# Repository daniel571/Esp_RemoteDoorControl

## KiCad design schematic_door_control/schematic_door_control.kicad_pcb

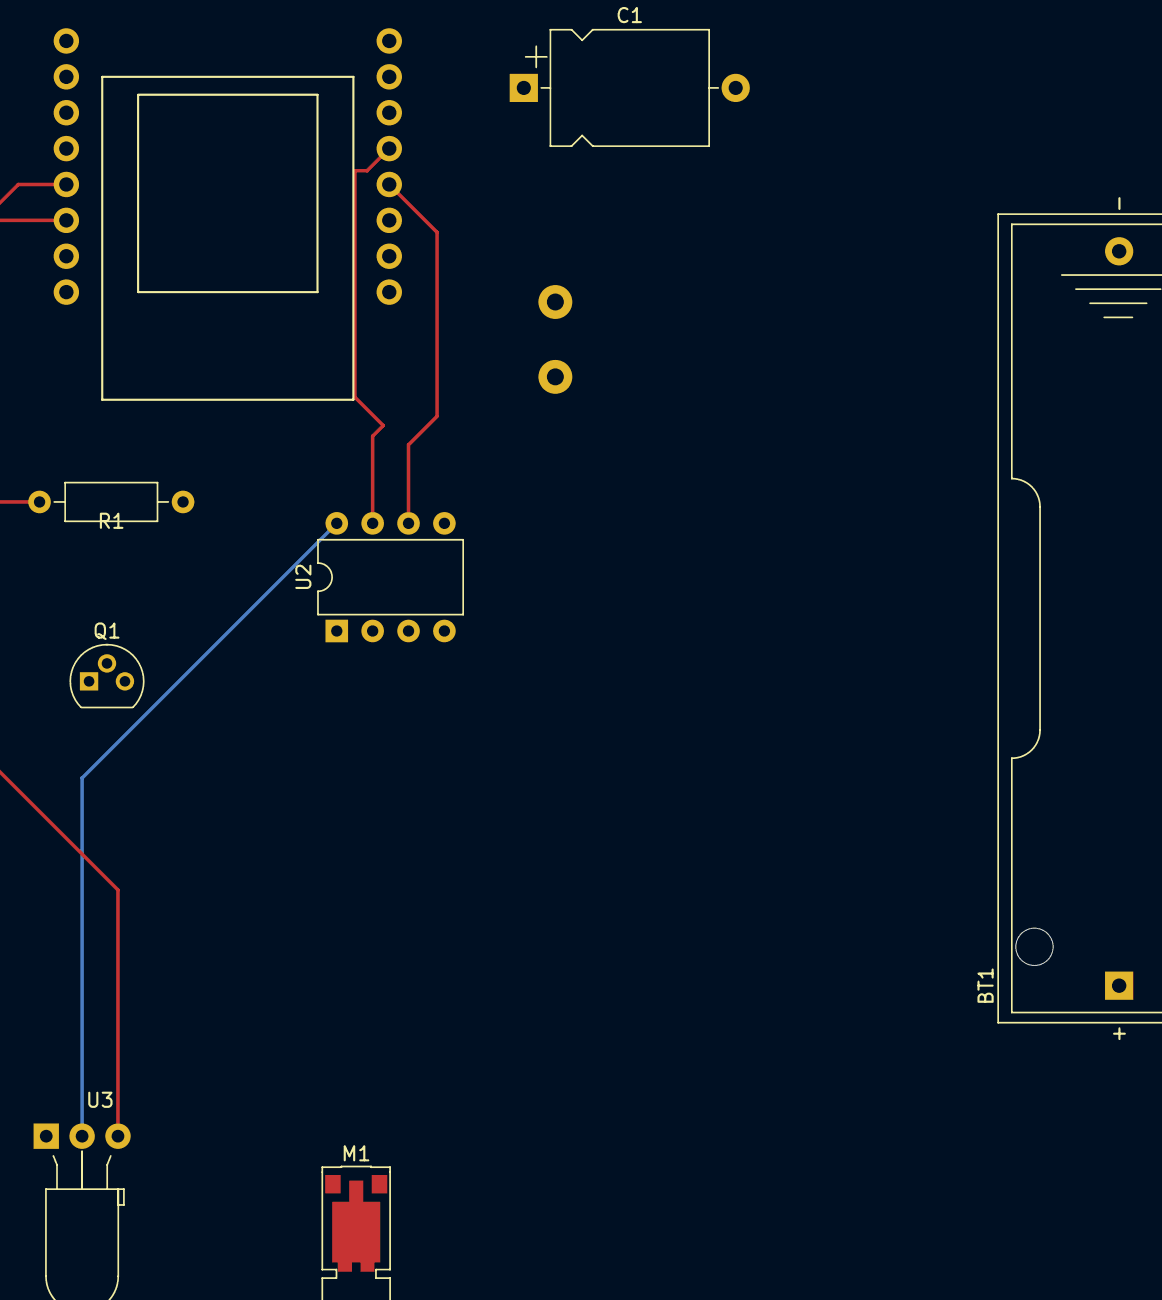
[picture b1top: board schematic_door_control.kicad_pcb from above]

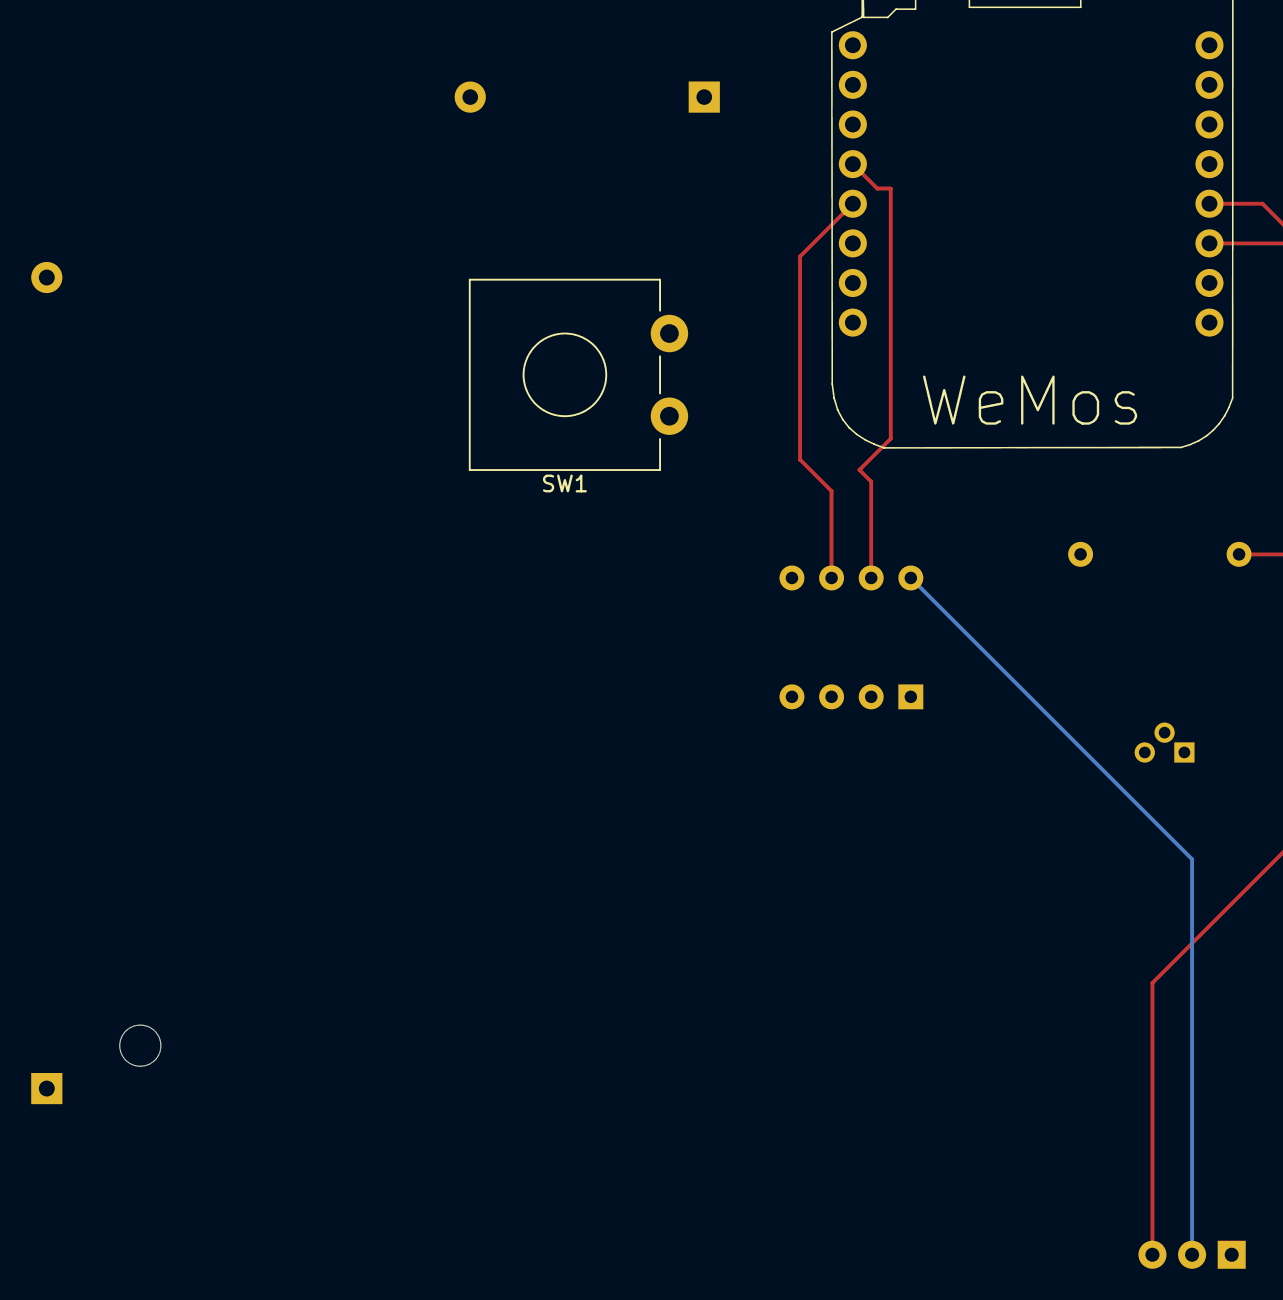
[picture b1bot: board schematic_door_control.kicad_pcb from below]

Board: 2 copper layers, 9 parts (2 on the bottom side), 12 nets.

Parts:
BT1: Battery; BatteryHolder_Keystone_2460_1xAA
C1: C_Polarized_Small_US; CP_Axial_L11.0mm_D8.0mm_P15.00mm_Horizontal
M1: Motor_DC; Vybronics_VZ30C1T8219732L
Q1: PNP; TO-92
R1: 2000; R_Axial_DIN0207_L6.3mm_D2.5mm_P10.16mm_Horizontal
SW1: SW_PUSH; SW_CW_GPTS203211B
U1: WeMos_mini; D1_mini_board
U2: L9110; DIP-8_W7.62mm
U3: ir; LED_D5.0mm-3_Horizontal_O3.81mm_Z3.0mm

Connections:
GND: BT1.2 (-), C1.2, SW1.1, U1.2 (GND), U2.5 (GND), U2.8 (GND), U3.2 (Vs-)
unnamed: BT1.1 (+), U2.2 (VCC), U2.3 (VCC)
unnamed: M1.1 (+), U2.1 (OA)
unnamed: M1.2 (-), U2.4 (OB)
unnamed: Q1.2 (B), R1.1
unnamed: Q1.1 (C), U3.1 (Vs+)
unnamed: C1.1, Q1.3 (E), U1.16 (3.3V)
unnamed: R1.2, U1.6 (D1)
unnamed: U1.5 (D2), U3.3 (OUT)
unnamed: U1.12 (D5), U2.6 (IA)
unnamed: U1.13 (D6), U2.7 (IB)
unnamed: SW1.2, U1.9 (Rst)

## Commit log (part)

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2024-08-17 Add http responses. Color of main button changes Add reverse button
2024-08-30 Version 2 - add EEPRON and configuraiton page
    Add EEPRON to save the configuration on the nvm.
    Add setting page (configuration) upon password to alter the direction and to change the hold off of reverse part.
2024-11-03 Door control SW version 3
    - Add smart rotation timeout based on reverse timer. But need to increase it
    - Add schematic and board files from kicad
    - Add button to signal when door is open or close as backup if IR detector is noisy
2026-04-11 IR removal
    1. IR removal
    - use magnet detector instead
    2. New IP
2026-04-11 Increasing the timeout
